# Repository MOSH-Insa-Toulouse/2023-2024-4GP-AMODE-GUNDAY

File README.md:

**Projet Capteur**

SOMMAIRE

[Introduction	](#_aqfiiiz3mat1)

[Circuit électronique	2](#_85kghymnccqe)

[Etude des filtres	3](#_3wv6rcoxo2u0)

[Modélisation du capteur:	5](#_od7riktkldgj)

[Schema complet:	6](#_dfu786f6gm2l)

[KICAD	6](#_9s9i8k258f05)

[Photo du circuit	11](#_kr2nya7ldd2s)

[Le programme Arduino	12](#_101d9m39fwqz)

[Application bluetooth	12](#_bzfua36c38m9)

[Banc de test	12](#_r0kbzpm251z9)

[Datasheet	12](#_eai4omgrnxa8)

[Discussions	12](#_o2hx32m0ftjm)

[Ameliorations	13](#_7aa4jqu1zgj3)

[Remerciements	13](#_hgrpjs9usncb)

# Introduction

Dans le cadre de l'UF "du capteur au banc de test" en 4ème année Génie Physique à l'INSA Toulouse, nous devions réaliser un capteur low-tech à base de graphite. Notre projet se base sur ce papier scientifique dont le but était de mesurer la résistance d’un capteur low-tech à base de graphite et déterminer son évolution au cours du temps en fonction de sa déformation. 

Ce répertoire comporte l’ensemble des étapes de réalisation.  

# Circuit électronique 

Le capteur que nous souhaitons utiliser pour ce projet est alimenté en 5V a une résistance de quelques dizaines megohms qui rend une mesure directe d’un courant de l’ordre 1 nA assez difficile avec les outils conventionnels. Ainsi il est nécessaire de passer par un circuit amplificateur. Pour cela nous avons utilisé un circuit de l'amplificateur transimpédance à  2 étages. 

Nous avons également utilisé 3 filtres pour réduire le bruit au maximum. Le schéma est présenté ci-dessous:

• R5 en entrée protège l'ampli opérationnel contre les décharges électrostatiques (il sera remplacé par notre capteur graphite)

• C1 avec R1 forme un filtre pour le bruit en courant 

• R2 pour une adaptation du calibre 

• C4 avec R3 forme un filtre actif 

• C2 avec R6 forme le filtre de sortie 

• C3 filtre le bruit d'alimentation (pour l'Arduino ce condensateur ne sera pas nécessaire)  

Le signal de la sortie en fonction de la résistance R5 s'écrit:

## Etude des filtres

Si nous ne mettons aucun filtres, nous obtiendrons la réponse suivante:

**Visualisation mesure filtre R1C1**

**Visualisation mesure filtre R3C4**

**Visualisation mesure filtre R6C2**

## Modélisation du capteur: 

## Schema complet: 

# KICAD

Nous avons utilisé le logiciel KICAD pour la réalisation de notre PCB. 

**Schématique et empreinte des composants que nous avons dû modéliser:** 

**Notre PCB:**

## **Photo du circuit**

# Le programme Arduino
Le programme Arduino permet de lire les valeurs de tension du capteur graphite et du capteur flex et de les envoyer par bluetooth. Il permet également d'ajuster le gain en recevant une valeur de l'application. 
# Application bluetooth

L'application à été développée avec le logiciel MIT App Inventor. Elle est dotée de fonctionnalités suivantes:

- Affichage de la résistance du capteur et du flex sensor
- Modification du gain du circuit
- Affichage de la datasheet

# Banc de test

L’objectif de ce banc de test est de déterminer la variation relative de résistance de notre capteur en fonction de la déformation appliquée. À l'aide d'une imprimante 3D, nous avons créé notre bande de test. Ensuite nous avons utilisé notre banc de test pour mesurer la résistance en fonction de la déformation.

D'après nos tests nous constatons que notre capteur donne des résultats acceptables.

# Datasheet
Pour la datasheet nous avons été inspirés par Texas Industries. 
# Discussions 

Ce projet nous a sensibilisé sur les technologies low-tech. Ces technologies écoresponsables et moins coûteuses peuvent devenir une alternative aux méthodes conventionnelles. Nous faire prendre conscience de cette démarche dès la 4ème année du cursus d’ingénieur nous aidera dans nos futurs métiers.  
# Ameliorations 
Lors de nos tests, nous avons remarqué que les capteurs n'étaient pas durables. Il serait intéressant d'effectuer des tests avec d’autres types de papier. 

# Remerciements
Nous souhaitons remercier le département de Génie Physique de l’INSA de Toulouse de nous avoir offert la chance de réaliser ce projet complet d’un capteur: de son développement jusqu’à sa caractérisation. Nous tenons tout particulièrement à remercier Jérémie Grisolia et Cathy Crouzet qui nous ont apporté leur aide pour mener à bien ce projet.

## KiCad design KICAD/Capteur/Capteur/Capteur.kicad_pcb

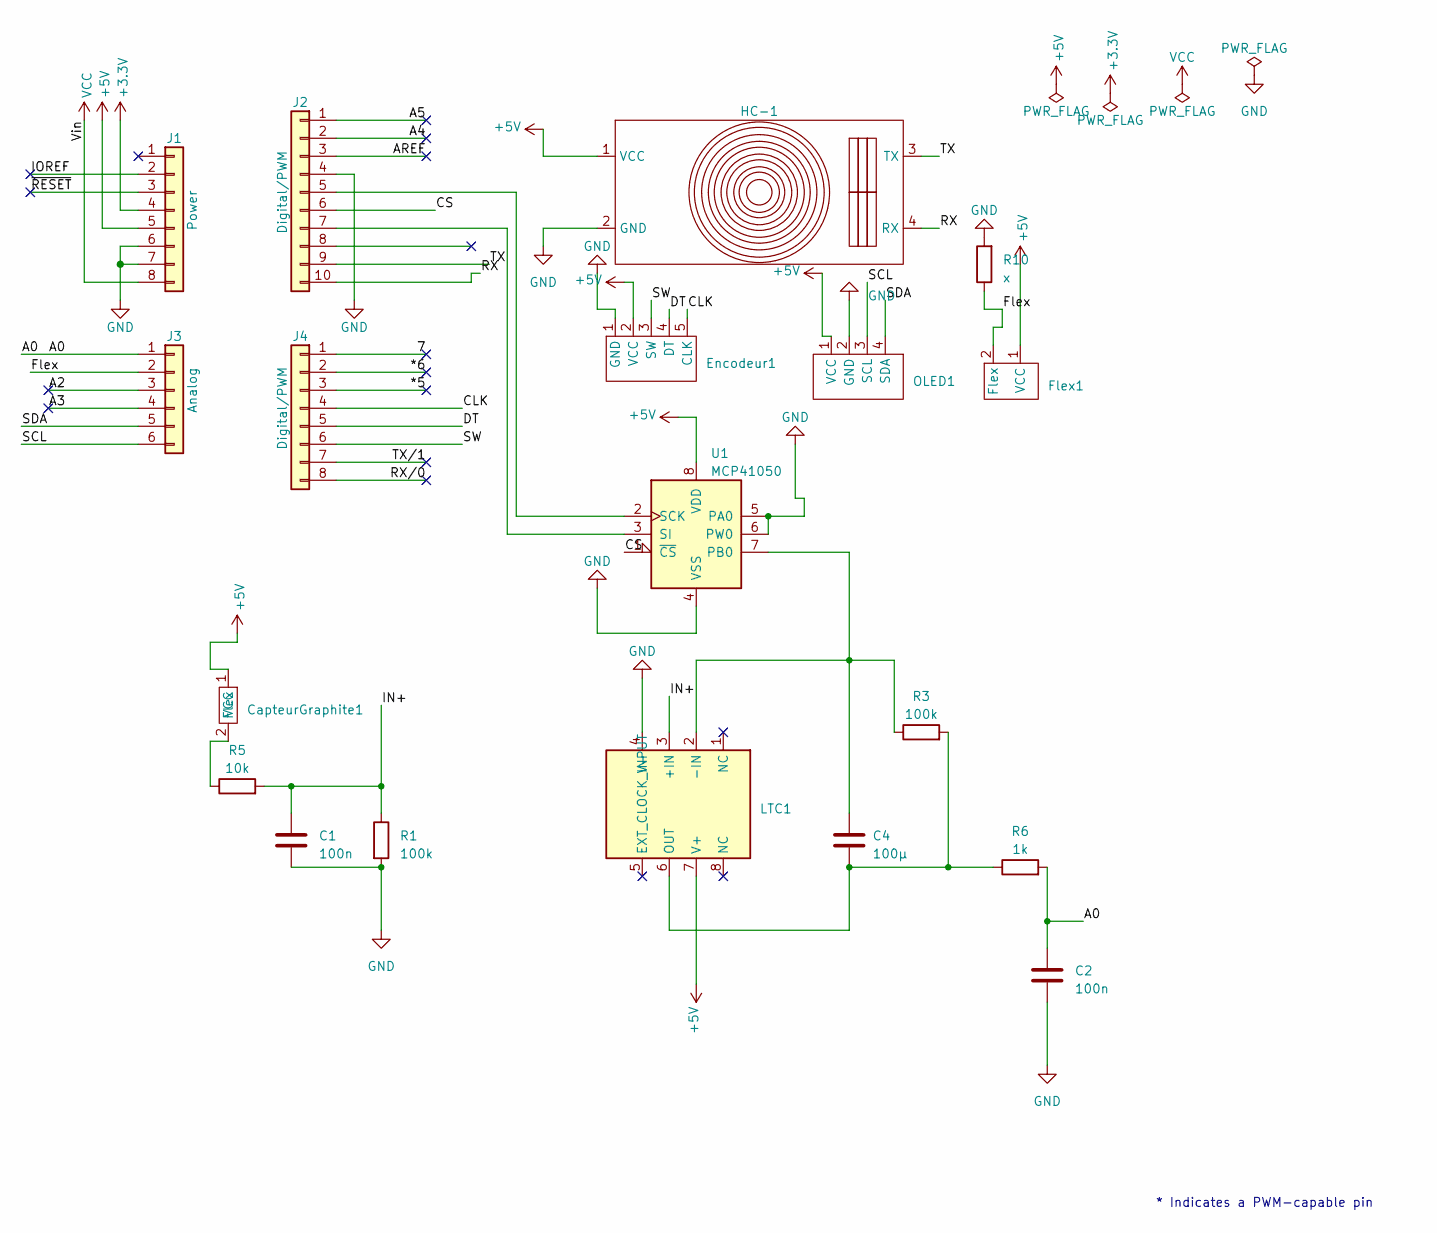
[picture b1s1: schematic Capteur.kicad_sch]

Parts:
C1, C2: 100n; CAPA
C4: 100µ; C_Rect_L7.0mm_W2.0mm_P5.00mm
CapteurGraphite1: Graphite
Encodeur1: Encodeur
Flex1: Flex
HC-1: Bluetooth
J1: Power; PinSocket_1x08_P2.54mm_Vertical
J2: Digital/PWM; PinSocket_1x10_P2.54mm_Vertical
J3: Analog; PinSocket_1x06_P2.54mm_Vertical
J4: Digital/PWM; PinSocket_1x08_P2.54mm_Vertical
LTC1: DIP-8_W7.62mm_LongPads
OLED1: OLED
R1, R3: 100k; CAPA
R5: 10k; CAPA
R6: 1k; CAPA
R10: x; CAPA
U1: MCP41050; DIP-8_W7.62mm_LongPads

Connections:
+3V3: J1.4
+5V: CapteurGraphite1.1 (VCC), Encodeur1.2 (VCC), Flex1.1 (VCC), HC-1.1 (VCC), J1.5, LTC1.7 (V+), OLED1.1 (VCC), U1.8 (VDD)
/7: J4.1
/*5: J4.3
/*6: J4.2
/A0: C2.1, J3.1, R6.2
/A2: J3.3
/A3: J3.4
/A4: J2.2
/A5: J2.1
/AREF: J2.3
/CLK: Encodeur1.5 (CLK), J4.4
/CS: J2.6, U1.1 (~CS)
/DT: Encodeur1.4 (DT), J4.5
/Flex: Flex1.2 (Flex), J3.2, R10.1
/IN+: C1.1, LTC1.3 (+IN), R1.1, R5.2
/IOREF: J1.2
/RX: HC-1.4 (RX), J2.10
/RX/0: J4.8
/SCL: J3.6, OLED1.3 (SCL)
/SDA: J3.5, OLED1.4 (SDA)
/SW: Encodeur1.3 (SW), J4.6
/TX: HC-1.3 (TX), J2.9
/TX/1: J4.7
/~RESET: J1.3
GND: C1.2, C2.2, Encodeur1.1 (GND), HC-1.2 (GND), J1.6, J1.7, J2.4, LTC1.4 (V-), OLED1.2 (GND), R1.2, R10.2, U1.4 (VSS), U1.5 (PA0), U1.6 (PW0)
unnamed: CapteurGraphite1.2 (Flex), R5.1
unnamed: J2.5, U1.2 (SCK)
unnamed: J2.7, U1.3 (SI)
unnamed: C4.1, LTC1.2 (-IN), R3.1, U1.7 (PB0)
unnamed: C4.2, LTC1.6 (OUT), R3.2, R6.1
VCC: J1.8

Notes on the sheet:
* Indicates a PWM-capable pin

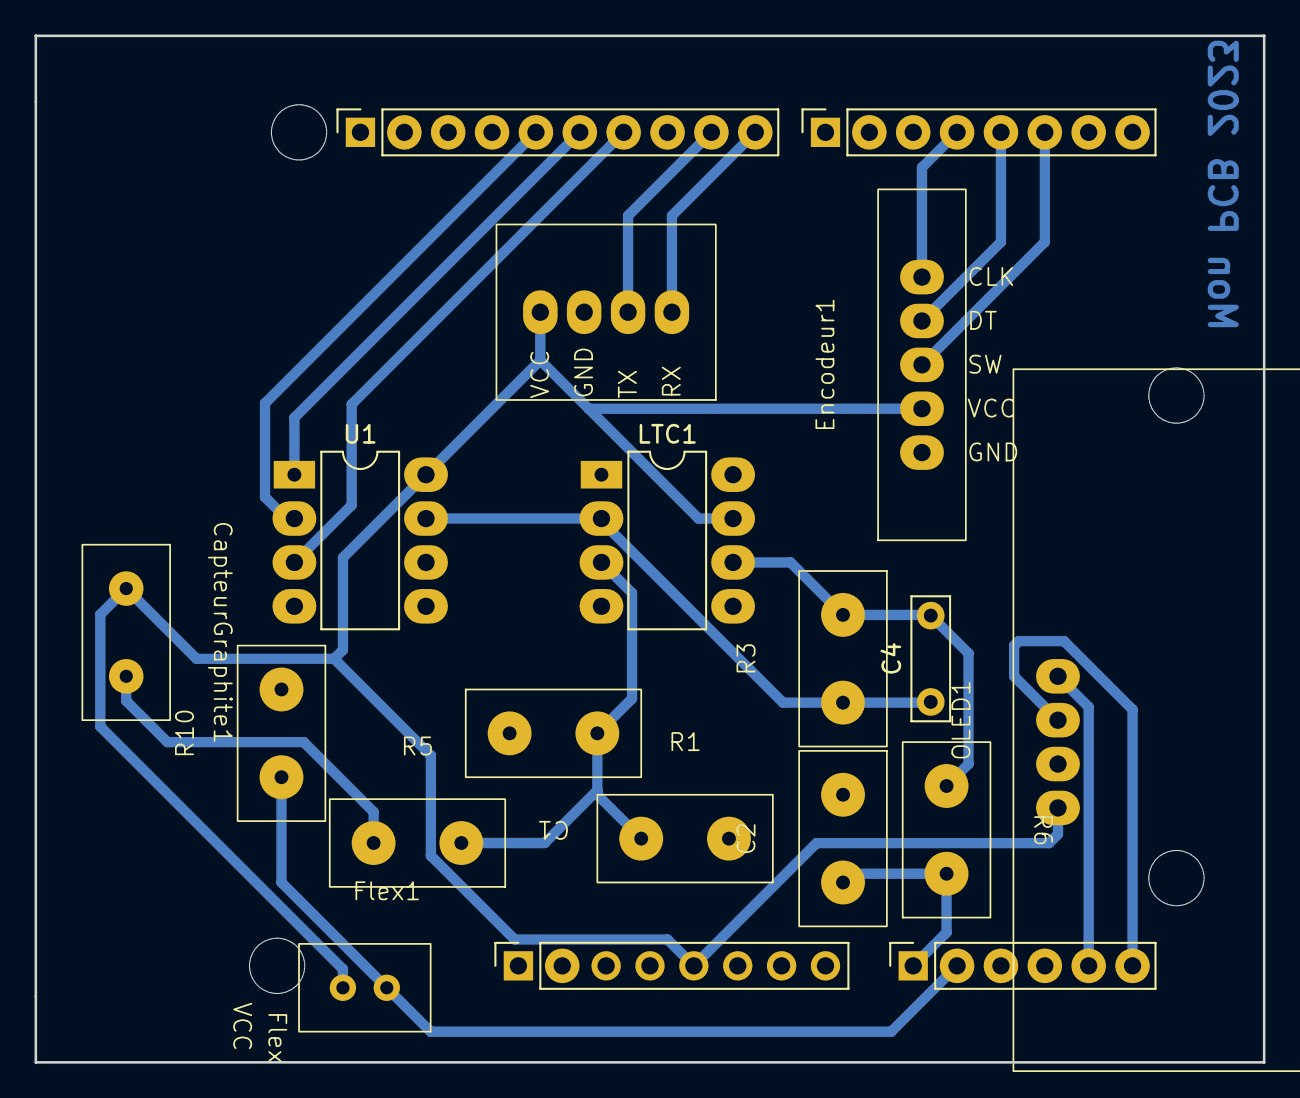
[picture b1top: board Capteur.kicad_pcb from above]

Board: 2 copper layers, 71.1 x 59.4 mm, 23 parts (0 on the bottom side), 18 nets.

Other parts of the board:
MH1, MH2, MH3, MH4: MountingHole_3.2mm

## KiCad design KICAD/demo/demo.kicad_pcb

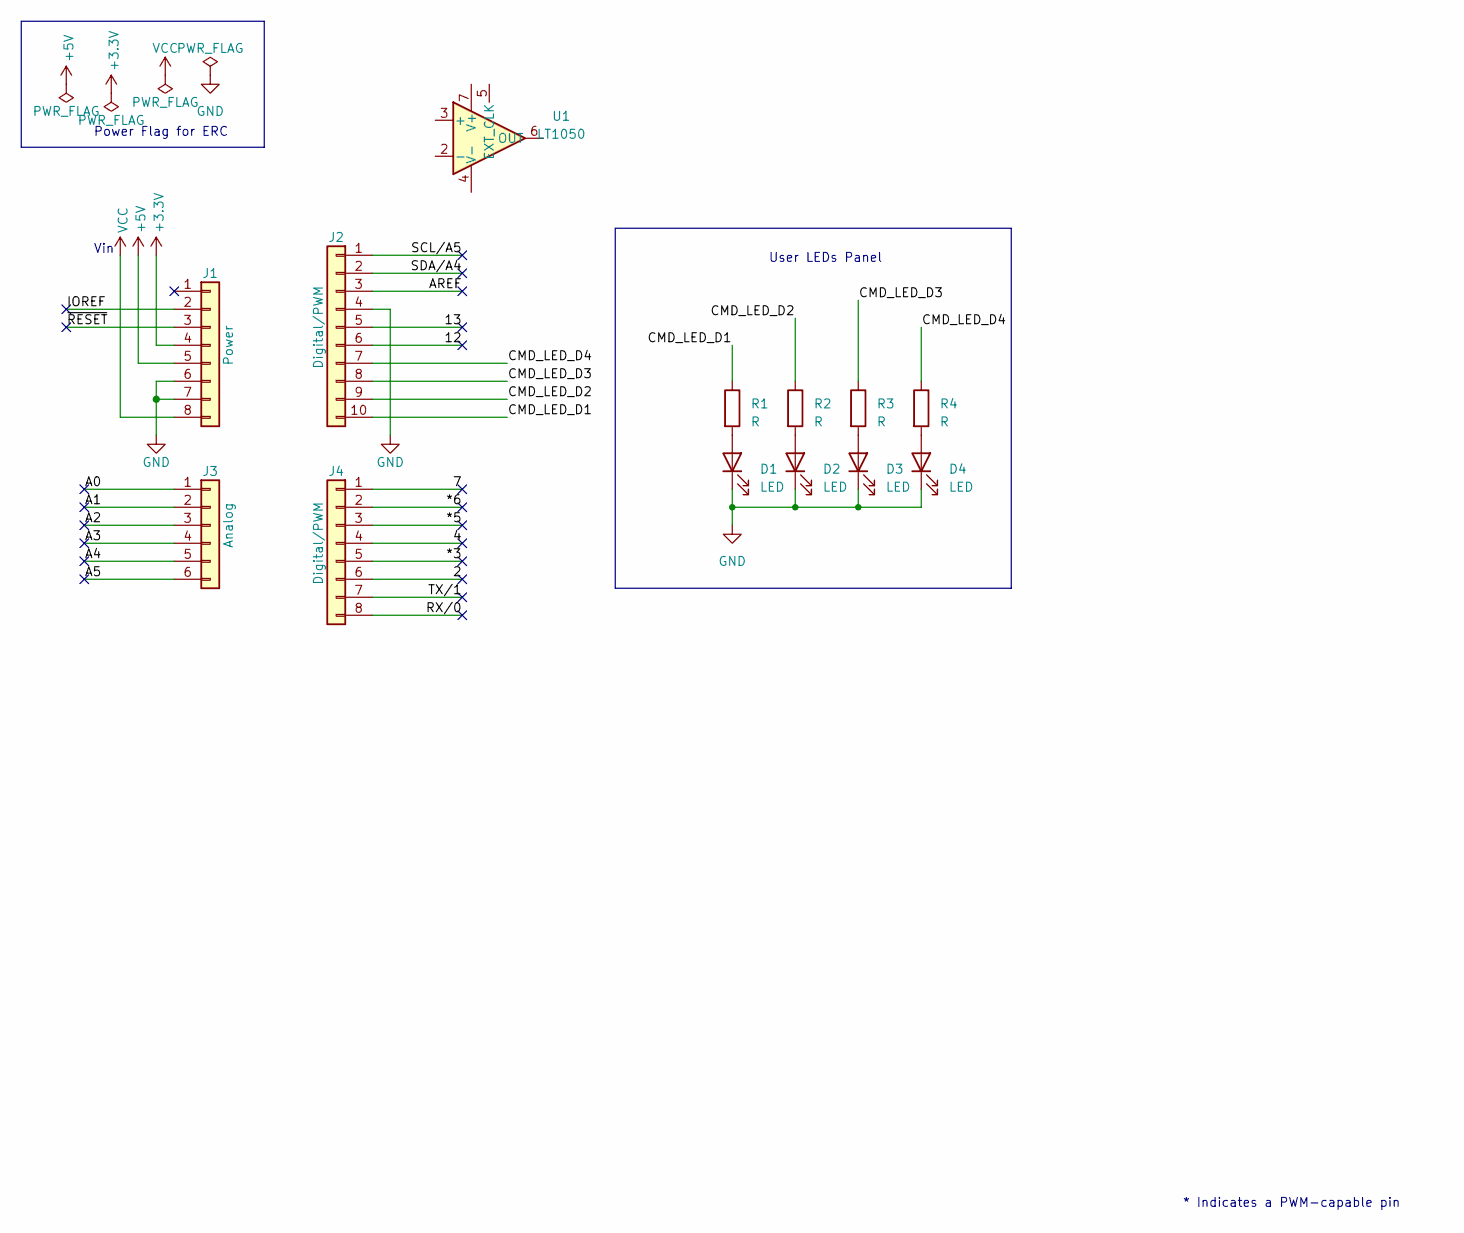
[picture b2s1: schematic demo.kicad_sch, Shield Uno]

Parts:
D1, D2, D3, D4: LED; LED_D5.0mm
J1: Power; PinSocket_1x08_P2.54mm_Vertical
J2: Digital/PWM; PinSocket_1x10_P2.54mm_Vertical
J3: Analog; PinSocket_1x06_P2.54mm_Vertical
J4: Digital/PWM; PinSocket_1x08_P2.54mm_Vertical
R1, R2, R3, R4: R; R_Axial_DIN0207_L6.3mm_D2.5mm_P10.16mm_Horizontal
U1: LT1050; DIP-8_W7.62mm_LongPads

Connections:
+3V3: J1.4
+5V: J1.5
/2: J4.6
/4: J4.4
/7: J4.1
/12: J2.6
/13: J2.5
/*3: J4.5
/*5: J4.3
/*6: J4.2
/A0: J3.1
/A1: J3.2
/A2: J3.3
/A3: J3.4
/A4: J3.5
/A5: J3.6
/AREF: J2.3
/CMD_LED_D1: J2.10, R1.1
/CMD_LED_D2: J2.9, R2.1
/CMD_LED_D3: J2.8, R3.1
/CMD_LED_D4: J2.7, R4.1
/IOREF: J1.2
/RX/0: J4.8
/SCL/A5: J2.1
/SDA/A4: J2.2
/TX/1: J4.7
/~RESET: J1.3
GND: D1.1 (K), D2.1 (K), D3.1 (K), D4.1 (K), J1.6, J1.7, J2.4
unnamed: D1.2 (A), R1.2
unnamed: D2.2 (A), R2.2
unnamed: D3.2 (A), R3.2
unnamed: D4.2 (A), R4.2
VCC: J1.8

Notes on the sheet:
User LEDs Panel
Power Flag for ERC
Vin
* Indicates a PWM-capable pin

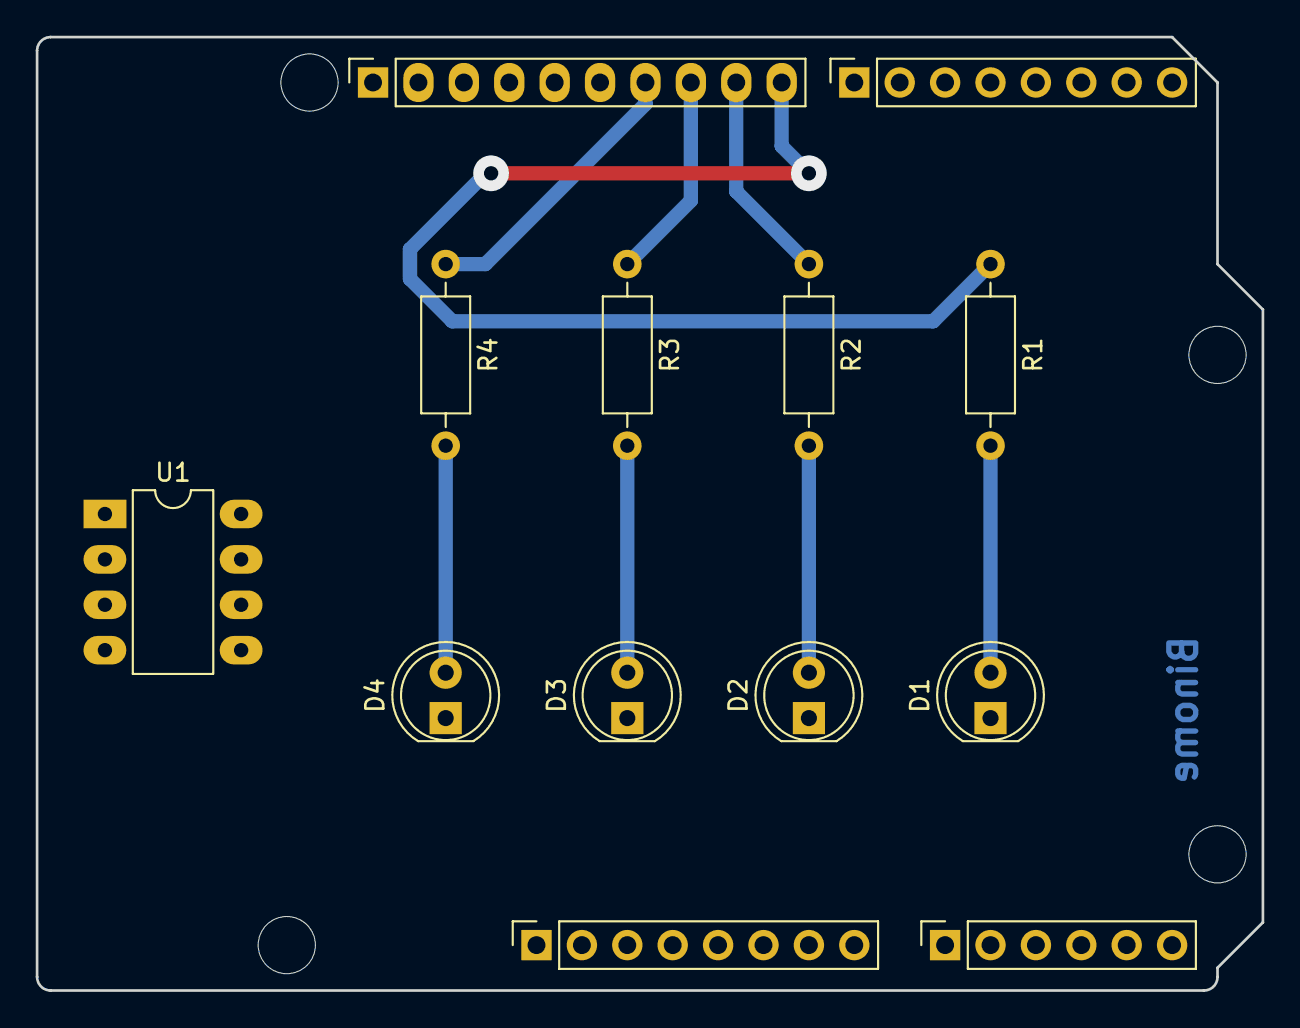
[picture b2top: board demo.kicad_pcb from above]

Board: 2 copper layers, 68.6 x 53.3 mm, 17 parts (0 on the bottom side), 9 nets.

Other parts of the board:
MH1, MH2, MH3, MH4: MountingHole_3.2mm

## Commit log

2023-02-03 test -Y
2023-02-03 ma commit
2023-02-03 Test test Test
2023-02-03 Test 2
2023-02-03 Test 3
2023-02-03 test4
2023-02-03 Bonjour
2023-02-03 TEST
2023-05-16 Add files via upload
    KICAD
2023-05-16 Add files via upload
    LTSPICE
2023-05-16 Add files via upload
    ANDROID
2023-05-16 Create Banc de Test
